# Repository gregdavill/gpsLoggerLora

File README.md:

# gpsLogger

	Project Stage: Firmware Devlopment
	v0.1a Prototyp Assembled
	Current Bugs:
	 * FLASH footprint wrong (fix in v0.2)
	 * Change BOM MCP73812 (CE pin) to MCP73832 (STATUS pin)
	 * Small changes to RF paths
	 * Update solderpaste apertures on X2SON parts (too much paste)
	 * Needs more test-points 
	 * LED colours B/G swapped

A basic portable GPS logger with LoRa wireless based on Microchip ATSAMR34

v0.1a PCB has been designed to accomidate both 433MHz and 868/915MHz bands. However support may be dropped for 433MHz in the future.

The PCB is design to fit in an existing enclosure used by a previous GPS datalogger.

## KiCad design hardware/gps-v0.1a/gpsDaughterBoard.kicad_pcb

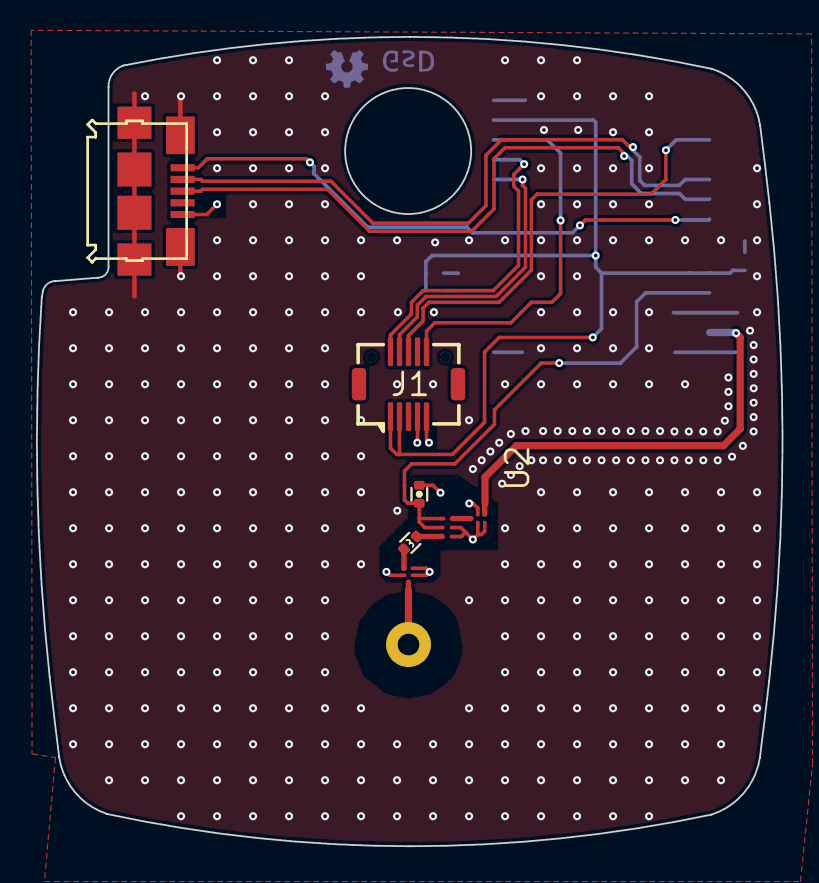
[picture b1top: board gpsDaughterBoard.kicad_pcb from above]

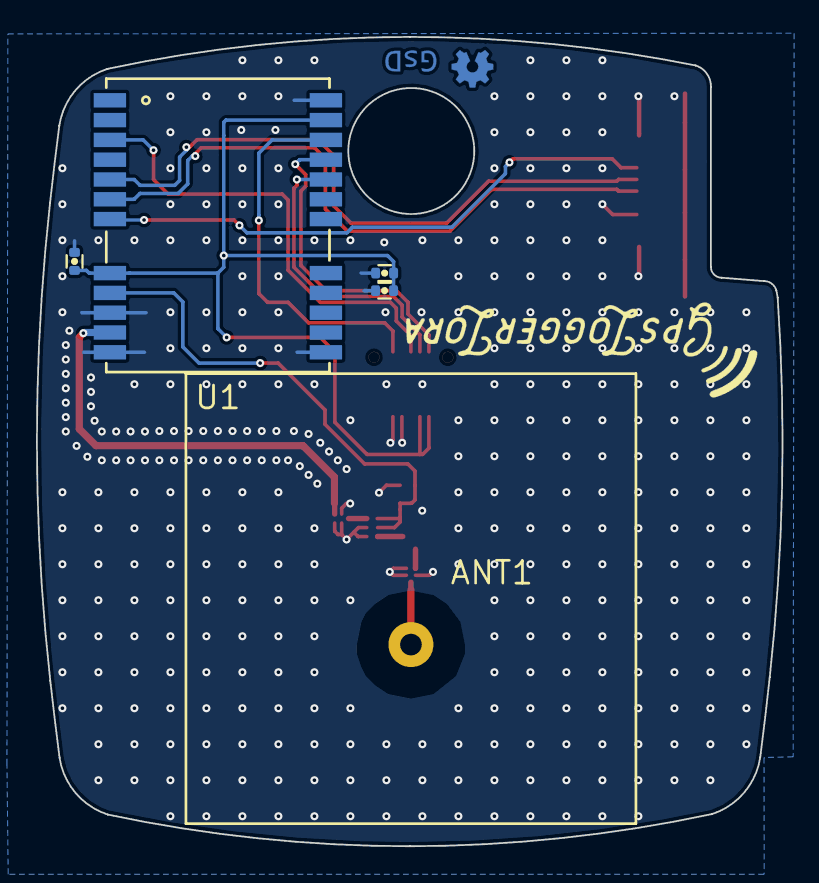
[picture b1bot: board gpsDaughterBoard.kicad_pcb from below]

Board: 4 copper layers, 41.4 x 45.0 mm, 12 parts (5 on the bottom side), 15 nets.

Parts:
ANT1: pkl_PATCH_ANTENNA; GPS_ANT
C1: 10nF; C_0402
C2, C3: 100nF; C_0402
C4: 1nF; C_0402
FLT1, FLT2: SF1186G; SAW-5
J1: JST DF12 10P; DF12(3.0)-10DS-0.5V(86)
J2: USB_OTG; Connector_USB_Micro_B_SMD
L1: 5.6nH; L_0402
U1: NEO_M8; NEO-M8
U2: BGU7007; XSON6

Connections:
+3V3: C1.1, C2.1, C3.1, J1.1, J1.3, U1.8, U1.23
/DATA_N: J2.2, U1.5
/DATA_P: J2.3, U1.6
/PPS: J1.6, U1.3
/RX: J1.4, U1.20
/TX: J1.2, U1.21
GND: C1.2, C2.2, C3.2, C4.2, FLT1.2, FLT1.4, FLT1.5, FLT2.2, FLT2.4, FLT2.5, J1.7, J1.9, J2.5, J2.GND, U1.10, U1.12, U1.13, U1.24, U2.4, U2.5
unnamed: ANT1.1, FLT2.1
unnamed: C4.1, U1.9, U2.1, U2.2
unnamed: FLT1.1, U2.6
unnamed: FLT1.3, U1.11
unnamed: FLT2.3, L1.2
unnamed: J1.10, U1.22
unnamed: J2.1, U1.7
unnamed: L1.1, U2.3

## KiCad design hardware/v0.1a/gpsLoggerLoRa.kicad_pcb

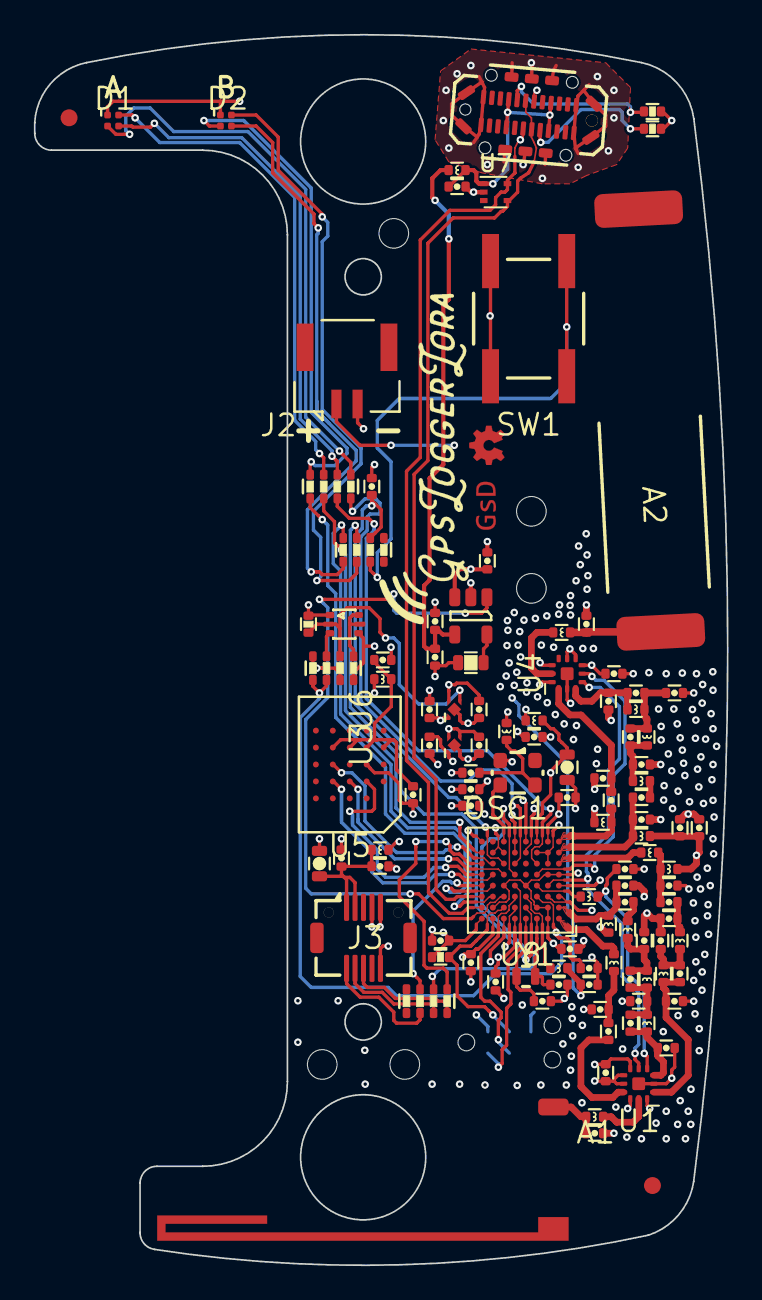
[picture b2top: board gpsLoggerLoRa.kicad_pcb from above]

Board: 4 copper layers, 40.9 x 72.7 mm, 111 parts (1 on the bottom side), 83 nets.

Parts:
A1: pkl_ANTENNA; 0900AT43A0070 - 900MHz Wide band ISM Chip Antenna
A2: pkl_ANTENNA; 0433AT62A0020 - 433MHz 25x5x1mm chip antenna
C1, C2, C3, C6, C11, C15, C32, C44, C47, C48, C52, C54, C55, C56: 100nF; C_0402
C4, C22, C27, C57, C59: 4.7pF; C_0402
C5, C21, C28, C29, C35, C39: DNP; C_0402
C7, C8, C18, C36, C40: 3.9pF; C_0402
C9: 10n; C_0402
C10, C13, C34: 22pF; C_0402
C12, C33, C38, C51: 18pF; C_0402
C14, C16, C17, C43, C53, C58: 1uF; C_0402
C19: 0R; C_0402
C20: 8.2pF; C_0402
C23: 4.7nF; C_0402
C24, C26: 6.8pF; C_0402
C25: 2.7pF; C_0402
C30: 33nF; C_0402
C31, C42: 1nF; C_0402
C37: 5.6pF; C_0402
C41: 3.3pF; C_0402
C45, C46: 10uF; C_0603
C49, C50: 10pF; C_0402
D1, D2: LED_ARGB; 0404LED_RGB
J1: USB_C_Receptacle; usbc_vert_10132328
J2: JST GH; BM02B-GHS-TBT
J3: DF12 - 10P; DF12(3.0)-10DP-0.5V(86)
J4: CTX TAG Connect; TC2030-NL_SMALL
L1: 18nH; L_0402
L2, L10, L22: 2.2nH; L_0402
L3, L4: 33nH; L_0402
L6: 82nH; L_0402
L7: 15nH; L_0402
L8: 12nH; L_0402
L9: 0R; L_0402
L11, L12: 11nH; L_0402
L13, L14, L15, L16, L23, L24: 10nH; L_0402
L17, L18, L19, L20, L21: 1k; L_0402
OSC1: TYETBCSANF-32.000000; Oscilator_2.5x2.0
Q1: FG6943010R; SOT-666
R1: 1k; R_0603
R2, R3, R4: 100R; R_Array_Concave_4x0603
R5, R7: 10k; R_0402
R6: 47k; R_Array_Concave_4x0603
R8, R9: 5.1k; R_0402
SW1: SW_Push; EVQ_switch
U1, U4: SKY13373; QFN-12-1EP_3x3mm_P0.5mm_EP1.65x1.65mm
U2: MCP73832; SOT-23-5
U3, U6: NCP167; X2SON_4_1.0x1.0mm
U5: MT25QL256ABA8E12; T-PBGA-24_6.0x8.0mm_Layout5x5_P1.0mm
U7: NUP2114; SOT-553
U8: ATSAMR34J18B; TFBGA-64_6.0x6.0mm_Layout8x8_P0.65mm
Y1: 32.768kHz; ABS05_32.768KHz Crystal

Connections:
+3V3: C2.2, C3.2, C6.2, C17.1, J3.10, J4.1, L18.1, R7.1, U3.1, U8.A7, U8.A8, U8.G4, U8.H8
/SAMR34/AUX_PWR_EN: C27.2, L24.1, Q1.2, R5.1, R6.6, U6.3
/SAMR34/BAND_SEL: C22.2, L23.1, U1.4
/SAMR34/BATTERY_VOLTAGE: C57.2, R6.1, R6.3, U8.C3
/SAMR34/CLK: J4.4, U8.C5
/SAMR34/DIO: J4.2, U8.D5
/SAMR34/FLASH_CLK: U5.B2, U8.E8
/SAMR34/FLASH_CS#: U5.C2, U8.E6
/SAMR34/GPS_PPS: R4.8, U8.F8
/SAMR34/GPS_RX: R4.6, U8.E5
/SAMR34/GPS_TX: R4.4, U8.D8
/SAMR34/LED_A_BLUE: R3.6, U8.G8
/SAMR34/LED_A_GREEN: R3.4, U8.F3
/SAMR34/LED_A_RED: R3.2, U8.F5
/SAMR34/LED_B_BLUE: R2.4, U8.B4
/SAMR34/LED_B_GREEN: R2.2, U8.C7
/SAMR34/LED_B_RED: R3.8, U8.D7
/SAMR34/PA_BOOST: L2.1, U8.F1
/SAMR34/PP3V3_AUX: C53.1, D1.1, D2.1, L19.2, L20.2, L21.2, U6.1
/SAMR34/RESET: J4.3, R7.2, U8.B6
/SAMR34/RFI_HF: L11.1, U8.A1
/SAMR34/RFI_LF: C59.1, L1.2, U8.H1
/SAMR34/RFO_HF: C7.2, C10.2, L3.1, U8.B1
/SAMR34/RFO_LF: C4.2, C19.2, L6.2, U8.G1
/SAMR34/RX\TX: U1.5, U4.4, U8.D2
/SAMR34/SHDN: U4.5, U8.E3
/SAMR34/USB_DATA_N: J1.A7, J1.B7, U7.5, U8.B8
/SAMR34/USB_DATA_P: J1.A6, J1.B6, U7.4, U8.C8
/SAMR34/USER_BUTTON: C56.1, R2.6, U8.F6
/SAMR34/VR_PA: C21.2, C23.2, L3.2, L4.1, L6.1, U8.D1
/USB/CHARGE_STAT: U2.1, U8.C6
/USB/VBAT: C15.1, C16.1, C52.1, J2.1, Q1.4, R6.7, U2.3, U3.3, U3.4, U6.4
/memio/DQ0: U5.D3, U8.F7
/memio/DQ1: U5.D2, U8.E7
AVDD: C1.2, C31.1, C42.1, C45.2, L18.2, U1.6, U4.6, U8.C1, U8.C2, U8.H3
GND: C1.1, C2.1, C3.1, C4.1, C5.1, C6.1, C7.1, C8.1, C9.2, C11.2, C13.1, C14.2, C15.2, C16.2, C17.2, C18.1, C20.1, C21.1, C22.1, C23.1, C24.1, C26.1, C27.1, C29.1, C30.2, C31.2, C32.2, C33.1, C36.1, C37.1, C40.1, C41.1, C42.2, C43.2, C44.2, C45.1, C46.2, C47.1, C48.1, C49.1, C50.2, C51.1, C52.2, C53.2, C54.2, C55.2, C56.2, C57.1, C58.1, J1.A1, J1.A12, J1.B1, J1.B12, J1.S1, J2.2, J3.7, J3.9, J4.5, L1.1, OSC1.2, Q1.1, R1.2, R5.2, R6.2, R6.5, R8.2, R9.2, SW1.2, U1.2, U1.7, U1.8, U1.10, U1.12, U1.13, U2.2, U3.2, U4.2, U4.7, U4.8, U4.10, U4.12, U4.13, U5.B3, U6.2, U7.2, U8.A2, U8.B2, U8.B3, U8.B5, U8.B7, U8.D4, U8.D6, U8.E1, U8.E2, U8.F2, U8.G2, U8.G3, U8.G5, U8.G6, U8.G7, U8.H5
unnamed: A1.1, C51.2, L22.2
unnamed: A2.1, C33.2, L10.2
unnamed: C5.2, C59.2, U4.1
unnamed: C9.1, J1.A4, J1.A9, J1.B4, J1.B9, L17.2, U7.1
unnamed: C10.1, L12.1
unnamed: C11.1, C14.1, L17.1, U2.4
unnamed: C8.2, C12.1, L2.2, L4.2
unnamed: C12.2, C18.2, L13.1
unnamed: C13.2, C34.2, L11.2
unnamed: C19.1, L7.1
unnamed: C20.2, C35.1, L12.2, L14.1
unnamed: C24.2, C25.1, L7.2, L8.1
unnamed: C25.2, C26.2, C28.1, L8.2, L9.1
unnamed: C28.2, C29.2, L9.2, U4.3
unnamed: C30.1, C32.1, U8.H2
unnamed: C34.1, U1.9
unnamed: C35.2, C37.2, C39.1, L14.2, L16.1
unnamed: C36.2, C38.1, L13.2, L15.1
unnamed: C38.2, C40.2, L15.2, U1.1
unnamed: C39.2, C41.2, L16.2, U1.3
unnamed: C43.1, C44.1, L19.1, U5.A4, U5.B4, U5.C4, U5.D4
unnamed: C46.1, C54.1, C55.1, J3.1, J3.3, L20.1
unnamed: C47.2, U8.H4
unnamed: C48.2, L21.1, OSC1.4
unnamed: C49.2, U8.A4, Y1.1
unnamed: C50.1, U8.A3, Y1.2
unnamed: C58.2, U8.A5
unnamed: D1.2, R3.1
unnamed: D1.3, R3.3
unnamed: D1.4, R3.5
unnamed: D2.2, R3.7
unnamed: D2.3, R2.1
unnamed: D2.4, R2.3
unnamed: J1.A5, R9.1
unnamed: J1.B5, R8.1
unnamed: J3.2, R4.3
unnamed: J3.4, R4.5
unnamed: J3.6, R4.7
unnamed: L10.1, U4.11
unnamed: L22.1, U1.11
unnamed: L23.2, U8.D3
unnamed: L24.2, U8.C4
unnamed: OSC1.3, U8.H6
unnamed: Q1.3, R6.4
unnamed: Q1.5, Q1.6, R6.8
unnamed: R1.1, U2.5
unnamed: R2.5, SW1.1

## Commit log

2018-12-27 Update gkl submodule
2018-12-27 Fixing up some errors after shuffle of libraries.
2018-12-28 Changed USB connector. Updated board outline. Updates to footprints to use 3d models. Add FLASH memory.
2018-12-28 First pass schematic done. Begin routing main board.
2018-12-28 First pass routing complete.
2018-12-29 Re-assigned IO pins. Added some extra filter as per Hardware guidelines.
2018-12-29 Remove .net from source control.
2018-12-29 Cleanup .gitignore. Remove all CCS MSP430 parts.
2018-12-29 Add outline dxf and lib-cache.
2018-12-29 Add initial version of gpsDaughterBoard.
2018-12-29 Small updates to the layout. Fixed up power planes. Passed DRC
2018-12-29 Added Vcore Cap. Missing from Microchips app note reference schematic
2018-12-29 First Pass routing GPS board
2018-12-29 Added TVS diode to USB input.
2018-12-29 Checked RF filters with reference schematics. Updated all Part Numbers for BOM.
2018-12-29 Update LED resistors to 330R to limit max current to 5mA
2018-12-29 Added BOM part numbers to GPS PCB.
2018-12-30 Finished routing the daughterboard.
2018-12-30 Fixed a DRC error in the GPS PCB. Small layout change to include a logo/product name on the PCB. Created a prototype 'panel' with both PCB attached for production.
2018-12-30 Updated GPS pcb with impoved RF path, and potetially easier to solder filters. Added USB connector to GPS pcb for debugging ublox.
2018-12-30 Re-do panel with new changes from GPS PCB.
2019-01-08 Add new hardware version v1.0b
2019-01-08 Fix to FLASH footprint.
2019-01-16 Added blank gcc firmware structiure.
